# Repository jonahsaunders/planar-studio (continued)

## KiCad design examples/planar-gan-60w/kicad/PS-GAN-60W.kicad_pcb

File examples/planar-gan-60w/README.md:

# PS-GAN-60W — A14

48 V nominal → isolated 12 V / 5 A **design target**, with an integrated GaN
half bridge and PCB transformer generated using Planar Studio. Native KiCad 10
schematic, PCB, local libraries, 3D models and reproducible scripts are included.

**Unbuilt engineering prototype. Full turnkey assembly and electrical release
are not confirmed.** Start with [the manufacturing review](Manufacturing-audit.html)
for the repaired CAD findings and remaining factory/qualification gates.

[Design review and copper-layer viewer](Review.html) · [Schematic PDF](Schematic.pdf) ·
[KiCad project](kicad/PS-GAN-60W.kicad_pro) · [Validation](VALIDATION.md)

## A14 manufacturing and routing audit

- Reoriented and lowered R11 to face Q2. Its output is a straight 1.840 mm
  connection, down from 3.367 mm. The driver-to-resistor trace drops from
  6.331 to 4.449 mm: combined explicit gate routing is **35% shorter**.
  The dedicated VSS pickup is rerouted around the relocated via.
- Widened the only 0.16 mm routed control launch to 0.20 mm. All explicit
  routed tracks are now at least 0.20 mm wide. Final pours preserve drive
  references, switching-node exclusions and connector soldering thermals.
- Refreshed all 43 exact electronic codes on 11 October. Every code has
  stock for five fitted boards before order-specific attrition; F1 (28 units)
  and L2 (39 units) have the lowest available quantities.
- Added 16 explicit fabrication/assembly-data screens, including connector
  annuli, BOM/CPL identity, mask clearances and every paste aperture. The
  smallest aperture area ratio is **0.7405** at a 0.125 mm stencil.
- JLC Standard PCBA publishes a 70 × 70 mm handling minimum, rails and
  fiducials. The supplied design remains a single 64 × 56 mm board.
  JLC must accept and provide the handling arrangement.
- Corrected duplicate manufacturing issue IDs and added a file-specific
  handoff. Core fitting, mating-plug delivery and full turnkey are unconfirmed.

[Turnkey readiness and handoff](TURNKEY-READINESS.html) ·
[Actual rectifier routing comparison](evidence/Rectifier-routing-before-after.png) ·
[A14 measurements](evidence/A14-layout-audit.json).

The A14 board contains 497 explicit track segments, 824.950 mm of summed
centerline length and 198 routed vias, including 50 ground stitches.
The six T1 transitions bring the filled/capped-hole requirement to 204.
Electronic identities, values and pin nets are unchanged; the schematic
remains A12. The inherited A13 feedback improvements below remain.

## A13 placement and direct routing (retained history)

- Turned and aligned the feedback/OVP resistor dividers so their connected pads
  face each other. R22/R23 and R27/R28 now have straight vertical connections.
- Repositioned the LED, shunt and compensation parts. All seven local feedback
  nets use top copper, with **11 signal vias removed**. Their combined explicit
  trace length falls from **80.9 to 49.9 mm** (38% shorter).
- Eight low-current resistors have one outward axial 0.20 mm neck per pad,
  equal lands/paste openings and at least 0.25 mm from land edge to via-hole edge.
  Branches stay off their lands. General ground stitching now avoids all R/C pads.
- Connected the GaN bypass capacitors directly, turned the GaN input-divider
  resistors to remove their U-shaped links, and shortened the bias ripple network.
- Removed obsolete waypoints from complete route chains. Across the board,
  native route segments fall from **797 to 501**, explicit trace
  length from **879.1 to 828.2 mm**, and routed vias from
  **211 to 197**. These are geometry measurements, not performance claims.
- Retained single-board manufacturing files, top-only electronics, winding
  artwork, mounting pattern, connector thermals and separate ground domains.

See the [routing and tombstoning review](ROUTING-ASSEMBLY-REVIEW.md),
[lower-left comparison](evidence/Feedback-routing-before-after.png) and
[native passive-entry audit](evidence/passive-routing-audit.json).

The [issue register](manufacturing-prototype/Manufacturing-issue-register.csv)
separates completed CAD corrections from factory process, service and hardware
qualification work. No electronic part identities or circuit values changed.

## Compact construction and bench access

The 64 × 56 mm chamfered board keeps all 75 purchased components on top
(73 SMT + two insertion headers). Four M3 mounts retain the other example's
exact exposed-substrate footprint on this design's **55 × 47 mm pattern**.
The hole spacing differs from the flyback example; the footprint geometry is reused.
Opposing 5.08 mm headers accept removable screw-terminal plugs. Pin 2 is positive
and pin 1 is return on both ports. Mark the cables to prevent a swap.

Six bare test pads provide VIN/PGND, VOUT/SGND and V5/AGND measurement pairs.
Connector bodies, plugs, wire bend radius and the lower ferrite half extend the
assembly envelope beyond the PCB. The header 3D meshes are simplified bodies;
physical mating/fixture clearance still needs review.

The 4:2:2 transformer places its repeatable windings inside the PCB, avoiding a
bobbin and hand-wound coil. Two secondary layers operate in parallel per half.
The tradeoff is an eight-layer heavy-copper construction with filled/capped
transitions, appreciable winding loss and coupling that needs measurement.
[Magnetic calculations](evidence/magnetics.json) report a **3.87 W nominal DC
winding-loss screen at 80 °C**, before AC copper/core loss. This is not a thermal
qualification or an efficiency prediction.

## Manufacturing files and five-board estimate

All 43 exact electronic catalog codes have 11 October snapshot stock for five fitted
boards before attrition. [Exact BOM and stock](sourcing/Manufacturing-parts-5boards.csv).
Stock is not reserved. Core halves and clips are specified from DigiKey;
removable plugs require an agreed accessory fitting/delivery operation. JLC
procurement/consignment and installation have not been accepted. Its parts
library does not guarantee delivery of loose accessories.

Allow **$400–650 total for five boards** ($80–130 each) as a planning estimate
for electronics assembly plus separate cores/clips/plugs. It excludes ferrite
fitting, functional testing, shipping, taxes and duties. The PCB/panel portion
is an engineering allowance; **there is no supplier quote**. Special-process
costs can exceed the allowance. [Itemized model](sourcing/Manufacturing-cost-5boards.csv).

- `manufacturing-prototype/` contains matched **single-board** exports and
  [construction/assembly notes](manufacturing-prototype/READ-BEFORE-ORDER.txt).
- JLCPCB must define and quote its assembly panel/rails for the 64 × 56 mm board.
  Review its final placement overlay and handling arrangement before release.
- Every 0.30 mm interconnect, including six T1 plated-pad transitions, is specified
  for resin fill, copper cap and planarization. Connector and mounting holes
  remain open. A single-board coordinate map identifies every drill treatment.
- Raw KiCad placement rotations require a supplier-model overlay. Review the
  U1 stencil example, mask registration, hidden-joint inspection and THT process.
- Depanelize after soldering/inspection and before fitting the core halves/clips.

No purchase, reservation, supplier message or fabrication upload was made.
A [supplier review draft](manufacturing-prototype/SUPPLIER-REVIEW-REQUEST.txt)
is included, not sent. The [82-reference ratings audit](COMPONENT-RATINGS.md)
retains electrical holds for magnetics, capacitors, input transients and startup/
fault protection. Clean CAD checks do not establish a working 60 W converter.

## Reproduction and provenance

`redraw_schematic.py` reconstructs the schematic from the manifest and bundled
symbols; `rebuild_board.py` generates the native routed board from the bundled
footprints and explicit placement/routing definitions. Use KiCad's Python for
pcbnew scripts. Run `audit_routing_and_silk.py` before `export_review.py`; the
export requires its matching PCB hash, then gates on clean ERC, DRC and parity.
The verified legend is exported directly without solder-mask clipping.
See [validation](VALIDATION.md) for the independent geometry/assembly audits.

`repair_manufacturing_footprints.py` reproduces the dimensioned library repairs.
The board generator and geometry audits require Shapely 2.x. Pass its installed
site-packages directory as the first argument when using KiCad Python.

`regenerate_magnetics.mjs` uses Node and a Planar Studio checkout passed as its
first argument. The original reference is repository commit
`71f6f4db9c1a7172bddca8c9c934d3a8ece2a481`. The importable
`planar-studio/T1.planar.json` is a four-section seed (P,S,S,P); the final
`T1-artwork.json` and `T1-windings.kicad_pcb` duplicate each secondary section
onto an adjacent layer. Importing the seed alone does not recreate the six
final winding layers. The winding review PCB is not the complete converter.

KiStack PCB, footprint, schematic, BOM and export guidance was
used. Official manufacturer and JLCPCB/LCSC sources were used directly with
the user's approval. [Source study](PER-DESIGN-STUDY.md),
[layout resources](DEEP-LAYOUT-REVIEW.md), [licenses](THIRD-PARTY-NOTICES.txt).
MIT PER, Rick Hartley, Robert Feranec and Phil's Lab are independent references;
no affiliation or endorsement is implied. Earlier review documents describe
historical revisions; this A13 guide and the current issue register take precedence.

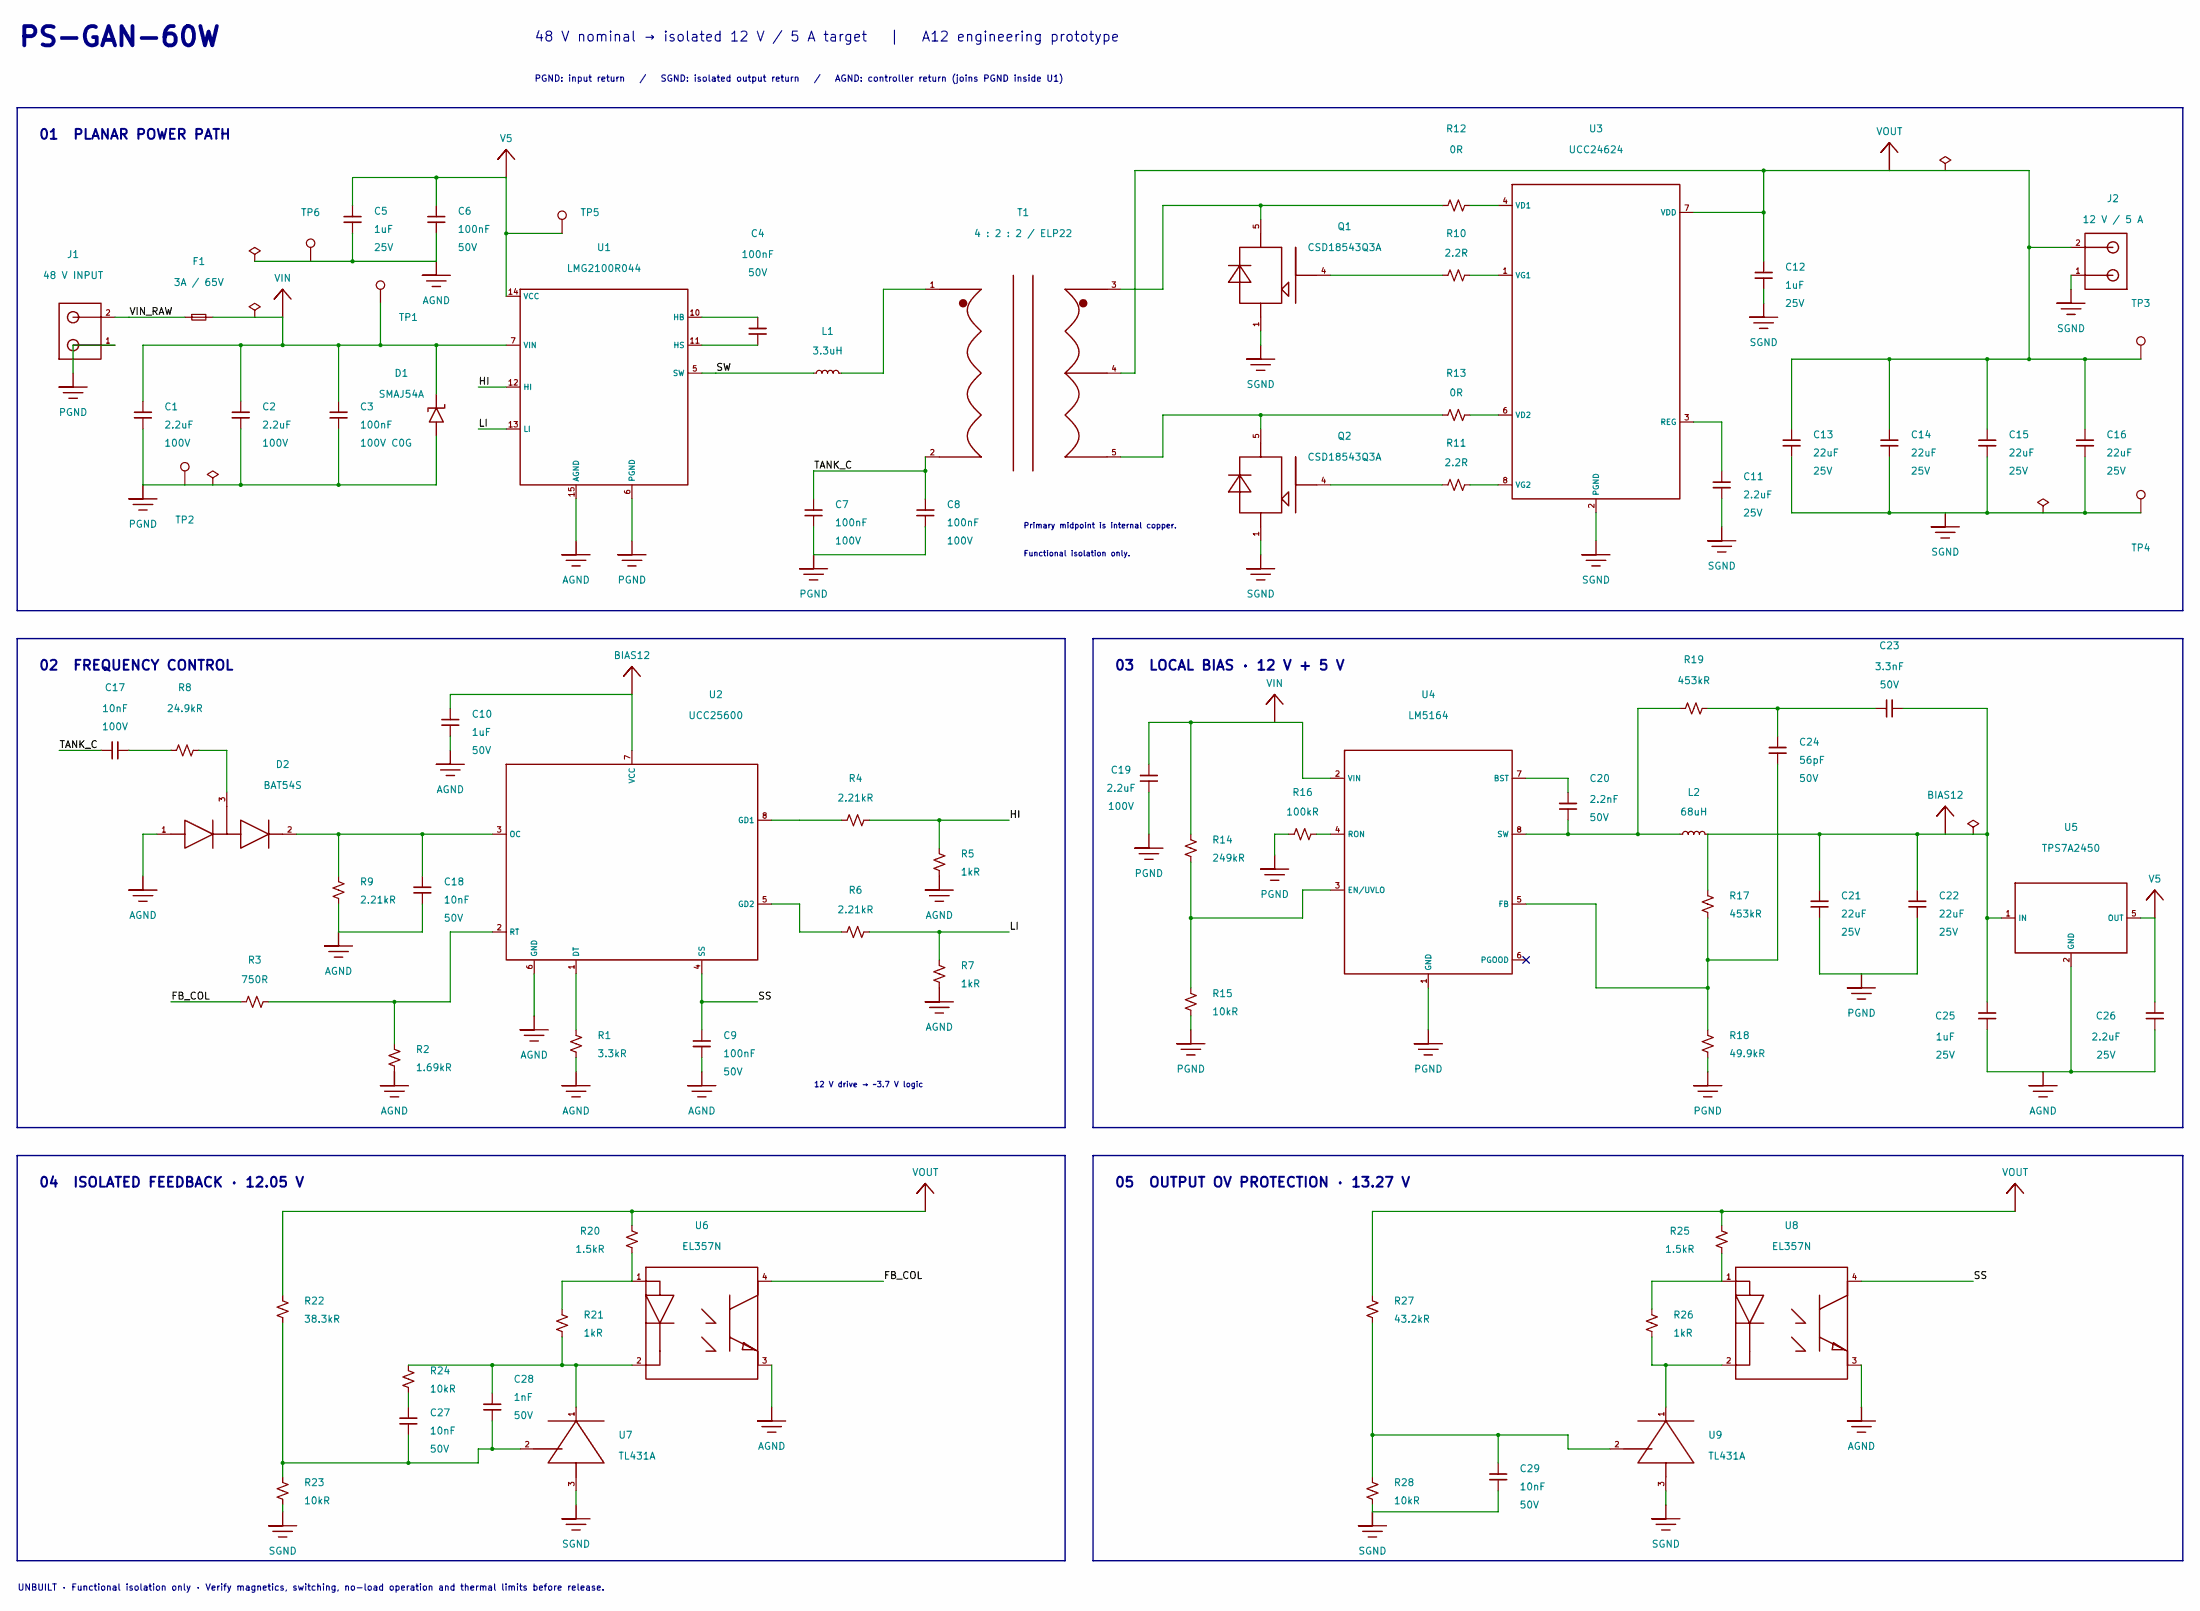
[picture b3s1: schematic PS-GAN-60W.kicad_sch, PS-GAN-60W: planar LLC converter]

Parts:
C1, C2, C19: 2.2uF; C_1210_3225Metric; Voltage 100V; MPN GRM32ER72A225KA35L; LCSC C86054
C3: 100nF; C_1206_3216Metric; Voltage 100V C0G; MPN GRM31C5C2A104JA01L; LCSC C405303
C4, C6, C9: 100nF; C_0603_1608Metric; Voltage 50V; MPN GRM188R71H104KA93D; LCSC C77055
C5, C12, C25: 1uF; C_0603_1608Metric; Voltage 25V; MPN GRM188R71E105KA12D; LCSC C86020
C7, C8: 100nF; C_1206_3216Metric; Voltage 100V; MPN GRM31C5C2A104JA01L; LCSC C405303
C10: 1uF; C_0805_2012Metric; Voltage 50V; MPN CL21B105KBFNNNE; LCSC C28323
C11, C26: 2.2uF; C_0805_2012Metric; Voltage 25V; MPN GRM21BR71E225KE11L; LCSC C77081
C13, C14, C15, C16, C21, C22: 22uF; C_1210_3225Metric; Voltage 25V; MPN GRM32ER71E226KE15L; LCSC C21397
C17: 10nF; C_0603_1608Metric; Voltage 100V; MPN CC0603KRX7R0BB103; LCSC C107059
C18, C27, C29: 10nF; C_0603_1608Metric; Voltage 50V; MPN CC0603KRX7R9BB103; LCSC C100042
C20: 2.2nF; C_0603_1608Metric; Voltage 50V; MPN CC0603JRNPO9BN222; LCSC C107043
C23: 3.3nF; C_0603_1608Metric; Voltage 50V; MPN GRM1885C1H332JA01D; LCSC C77036
C24: 56pF; C_0603_1608Metric; Voltage 50V; MPN CC0603JRNPO9BN560; LCSC C107053
C28: 1nF; C_0603_1608Metric; Voltage 50V; MPN CC0603JRNPO9BN102; LCSC C106246
D1: SMAJ54A; SMA_L4.4-W2.6-LS5.0-RD; MPN SMAJ54A-13-F; LCSC C134996
D2: BAT54S; SOT-23_L2.9-W1.3-P1.90-LS2.4-BR; MPN BAT54SLT1G; LCSC C19726
F1: 3A / 65V; F1206; MPN SF-1206F300M-2; LCSC C3177336
J1: 48 V INPUT; CONN-TH_2P-P5.08_WJ2EDGRC-5.08-2P; MPN WJ2EDGRC-5.08-02P-14-00A; LCSC C3697
J2: 12 V / 5 A; CONN-TH_2P-P5.08_WJ2EDGRC-5.08-2P; MPN WJ2EDGRC-5.08-02P-14-00A; LCSC C3697
L1: 3.3uH; L_Bourns_SRP5030T; MPN SRP5030T-3R3M; LCSC C189931
L2: 68uH; L_Bourns_SRP7050TA; MPN SRP7050TA-680M; LCSC C2047750
Q1, Q2: CSD18543Q3A; VSONP-8_L3.1-W3.1-P0.65-LS3.5-BL; MPN CSD18543Q3A; LCSC C840100
R1: 3.3kR; R_0603_1608Metric; MPN RC0603FR-073K3L; LCSC C108078
R2: 1.69kR; R_0603_1608Metric; MPN RC0603FR-071K69L; LCSC C185356
R3: 750R; R_0603_1608Metric; MPN RC0603FR-07750RL; LCSC C114635
R4, R6, R9: 2.21kR; R_0603_1608Metric; MPN RC0603FR-072K21L; LCSC C273748
R5, R7, R21, R26: 1kR; R_0603_1608Metric; MPN RC0603FR-071KL; LCSC C22548
R8: 24.9kR; R_0603_1608Metric; MPN RC0603FR-0724K9L; LCSC C137761
R10, R11: 2.2R; R_0603_1608Metric; MPN RC0603FR-072R2L; LCSC C112307
R12, R13: 0R; R_0603_1608Metric; MPN RC0603FR-070RL; LCSC C100044
R14: 249kR; R_0603_1608Metric; MPN RC0603FR-07249KL; LCSC C137763
R15, R23, R24, R28: 10kR; R_0603_1608Metric; MPN RC0603FR-0710KL; LCSC C98220
R16: 100kR; R_0603_1608Metric; MPN RC0603FR-07100KL; LCSC C14675
R17, R19: 453kR; R_0603_1608Metric; MPN RC0603FR-07453KL; LCSC C273765
R18: 49.9kR; R_0603_1608Metric; MPN RC0603FR-0749K9L; LCSC C114624
R20, R25: 1.5kR; R_0603_1608Metric; MPN ERJPA3F1501V; LCSC C543357
R22: 38.3kR; R_0603_1608Metric; MPN RC0603FR-0738K3L; LCSC C137736
R27: 43.2kR; R_0603_1608Metric; MPN RC0603FR-0743K2L; LCSC C137720
T1: 4 : 2 : 2 / ELP22; Planar_ELP22_4_2_2
TP1: VIN; Probe_ENIG_1.2mm
TP2: PGND; Probe_ENIG_1.2mm
TP3: VOUT; Probe_ENIG_1.2mm
TP4: SGND; Probe_ENIG_1.2mm
TP5: V5; Probe_ENIG_1.2mm
TP6: AGND; Probe_ENIG_1.2mm
U1: LMG2100R044; QFN-17_L5.5-W4.5-P0.50-TL_LMG2100R044; MPN LMG2100R044RARR; LCSC C22453052
U2: UCC25600; SOIC-8_L4.9-W3.9-P1.27-LS6.0-BL; MPN UCC25600DR; LCSC C130223
U3: UCC24624; SOIC-8_L4.9-W3.9-P1.27-LS6.0-BL; MPN UCC24624DR; LCSC C2862446
U4: LM5164; SO-8_L4.9-W3.9-P1.27-LS6.0-BL-EP; MPN LM5164DDAR; LCSC C477928
U5: TPS7A2450; SOT-23-5_L2.9-W1.6-P0.95-LS2.8-BR; MPN TPS7A2450DBVR; LCSC C2864436
U6, U8: EL357N; OPTO-SMD-4_L4.4-W4.1-P2.54-LS7.0-BL; MPN EL357N(A)(TA)-VG; LCSC C359074
U7, U9: TL431A; SOT-23-3_L2.9-W1.6-P1.90-LS2.8-BR; MPN TL431AIDBZR; LCSC C23892

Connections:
/FB_COL: R3.2, U6.4 (COL)
/HI: R4.2, R5.1, U1.12 (HI)
/LI: R6.2, R7.1, U1.13 (LI)
/SS: C9.1, U2.4 (SS), U8.4 (COL)
/SW: L1.1, U1.5 (SW)
/TANK_C: C7.1, C8.1, C17.1, T1.2 (P_END)
/VIN_RAW: F1.1, J1.2
AGND: C5.2, C6.2, C9.2, C10.2, C18.2, C25.2, C26.2, D2.1 (A), R1.2, R2.2, R5.2, R7.2, R9.2, TP6.1, U1.15 (AGND), U2.6 (GND), U5.2 (GND), U6.3 (EM), U8.3 (EM)
BIAS12: C10.1, C21.1, C22.1, C23.2, C25.1, L2.2, R17.1, U2.7 (VCC), U5.1 (IN), U5.3 (EN)
unnamed: C17.2, R8.1
unnamed: C23.1, C24.1, R19.2
unnamed: C27.1, R24.2
unnamed: D2.3 (A/C), R8.2
unnamed: C18.1, D2.2 (C), R9.1, U2.3 (OC)
unnamed: Q1.4 (G), R10.2
unnamed: Q2.4 (G), R11.2
unnamed: L1.2, T1.1 (P_DOT)
unnamed: Q1.5 (D), Q1.6 (D), Q1.7 (D), Q1.8 (D), Q1.9 (D), R12.1, T1.3 (S_DOT)
unnamed: Q2.5 (D), Q2.6 (D), Q2.7 (D), Q2.8 (D), Q2.9 (D), R13.1, T1.5 (S_END)
unnamed: C4.1, U1.10 (HB)
unnamed: C4.2, U1.11 (HS)
unnamed: R1.1, U2.1 (DT)
unnamed: R4.1, U2.8 (GD1)
unnamed: R6.1, U2.5 (GD2)
unnamed: R2.1, R3.1, U2.2 (RT)
unnamed: C11.1, U3.3 (REG)
unnamed: R12.2, U3.4 (VD1)
unnamed: R13.2, U3.6 (VD2)
unnamed: R10.1, U3.1 (VG1)
unnamed: R11.1, U3.8 (VG2)
unnamed: C20.1, U4.7 (BST)
unnamed: R14.2, R15.1, U4.3 (EN/UVLO)
unnamed: C24.2, R17.2, R18.1, U4.5 (FB)
unnamed: R16.2, U4.4 (RON)
unnamed: C20.2, L2.1, R19.1, U4.8 (SW)
unnamed: R20.2, R21.1, U6.1 (AN)
unnamed: C28.1, R21.2, R24.1, U6.2 (CA), U7.1 (CATHODE)
unnamed: C27.2, C28.2, R22.2, R23.1, U7.2 (REF)
unnamed: R25.2, R26.1, U8.1 (AN)
unnamed: R26.2, U8.2 (CA), U9.1 (CATHODE)
unnamed: C29.1, R27.2, R28.1, U9.2 (REF)
PGND: C1.2, C2.2, C3.2, C7.2, C8.2, C19.2, C21.2, C22.2, D1.2 (A), J1.1, R15.2, R16.1, R18.2, TP2.1, U1.6 (PGND), U1.17 (PGND), U4.1 (GND), U4.9 (EP)
SGND: C11.2, C12.2, C13.2, C14.2, C15.2, C16.2, C29.2, J2.1, Q1.1 (S), Q1.2 (S), Q1.3 (S), Q2.1 (S), Q2.2 (S), Q2.3 (S), R23.2, R28.2, TP4.1, U3.2 (PGND), U3.5 (VSS), U7.3 (ANODE), U9.3 (ANODE)
V5: C5.1, C6.1, C26.1, TP5.1, U1.14 (VCC), U5.5 (OUT)
VIN: C1.1, C2.1, C3.1, C19.1, D1.1 (K), F1.2, R14.1, TP1.1, U1.7 (VIN), U4.2 (VIN)
VOUT: C12.1, C13.1, C14.1, C15.1, C16.1, J2.2, R20.1, R22.1, R25.1, R27.1, T1.4 (S_CT), TP3.1, U3.7 (VDD)

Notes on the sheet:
PS-GAN-60W
48 V nominal → isolated 12 V / 5 A target | A12 engineering prototype
PGND: input return / SGND: isolated output return / AGND: controller return (joins PGND inside U1)
01 PLANAR POWER PATH
Primary midpoint is internal copper.
Functional isolation only.
02 FREQUENCY CONTROL
12 V drive → ~3.7 V logic
03 LOCAL BIAS · 12 V + 5 V
04 ISOLATED FEEDBACK · 12.05 V
05 OUTPUT OV PROTECTION · 13.27 V
UNBUILT · Functional isolation only · Verify magnetics, switching, no-load operation and thermal limits before release.

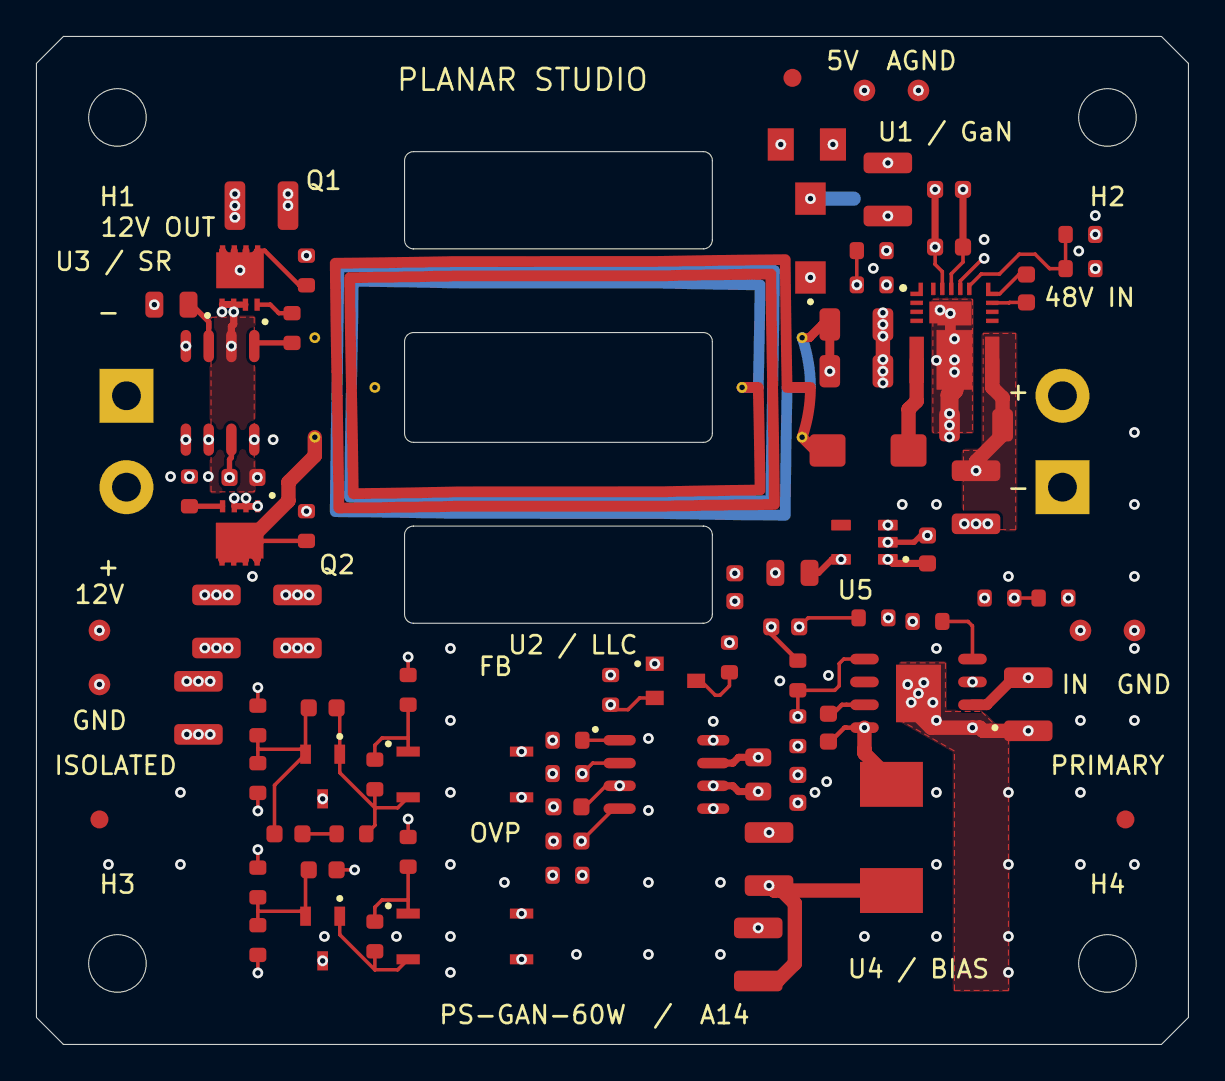
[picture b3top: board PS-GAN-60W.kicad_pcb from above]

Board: 8 copper layers, 64.0 x 56.0 mm, 89 parts (0 on the bottom side), 46 nets.

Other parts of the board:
FID1, FID2, FID3: Fiducial_1mm_Mask3mm
H1, H2, H3, H4: M3 / NPTH 3.2mm; MountingHole_3.2mm_M3_ExposedSubstrate_Edge
